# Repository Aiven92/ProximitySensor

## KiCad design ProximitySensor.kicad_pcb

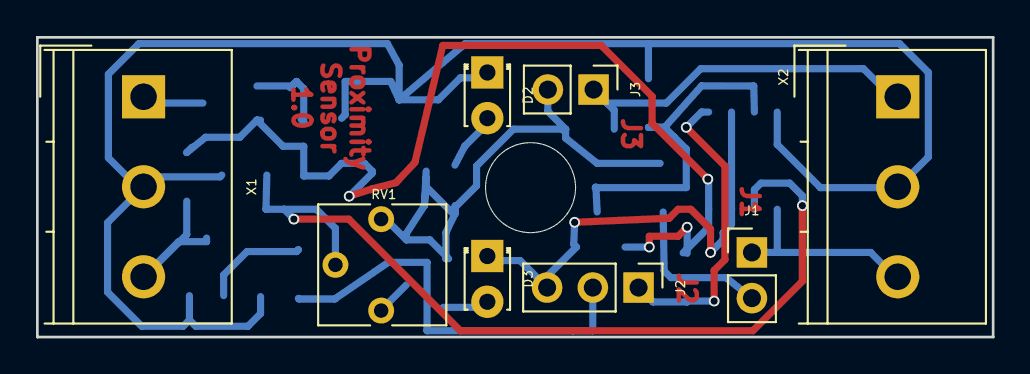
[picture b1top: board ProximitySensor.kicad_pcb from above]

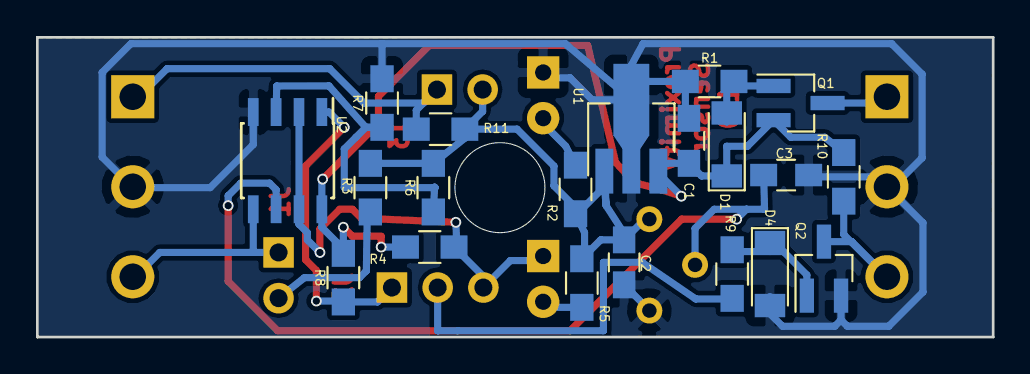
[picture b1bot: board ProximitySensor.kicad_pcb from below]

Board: 2 copper layers, 53.1 x 16.7 mm, 28 parts (20 on the bottom side), 17 nets.

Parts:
C1: 0,33uF; C_0805_HandSoldering
C2, C3: 0,1uF; C_0805_HandSoldering
D1, D4: D_Zener; D_MiniMELF
D2: LED_POWER; LED_D1.8mm_W3.3mm_H2.4mm
D3: LED_SIGNAL; LED_D1.8mm_W3.3mm_H2.4mm
J1, J3: Conn_01x02_Male; Pin_Header_Straight_1x02_Pitch2.54mm
J2: Conn_01x03_Male; Pin_Header_Straight_1x03_Pitch2.54mm
Q1: Q_PMOS_GSD; SOT-23_Handsoldering
Q2: Q_NMOS_GSD; SOT-23_Handsoldering
R1: 100k; R_0805_HandSoldering
R2, R5, R11: 1K; R_0805_HandSoldering
R3, R4, R6, R7, R8, R10: 10K; R_0805_HandSoldering
R9: 100R; R_0805_HandSoldering
RV1: 10k; Potentiometer_Trimmer_Vishay_T73YP_Horizontal
U1: L78L05_SOT89; SOT-89-3_Handsoldering
U2: LM393; SOIC-8_3.9x4.9mm_Pitch1.27mm
X1, X2: CONN_3; TerminalBlock_Philmore_TB133_03x5mm_Straight

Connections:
/5v: C2.1, J3.2, R2.1, R3.1, R5.1, R6.1, R11.2, RV1.1, U1.1
/Gnd: C1.2, C2.2, C3.2, D2.1, D4.2, Q2.2, R1.2, R7.2, RV1.3, U1.2, U2.4, X1.2, X2.2
/Vcc: C1.1, D1.1, Q1.2, R4.1, R8.2, R10.2, U1.3, U2.8
/in_v: Q1.3, X1.1
/sign: J1.1, U2.5, X2.3
unnamed: C3.1, RV1.2, U2.6
unnamed: D1.2, Q1.1, R1.1
unnamed: D2.2, R2.2
unnamed: D3.1, J2.3, R4.2, U2.2, U2.7
unnamed: D3.2, R5.2
unnamed: D4.1, Q2.1, R9.2
unnamed: J1.2, R3.2
unnamed: J2.1, R8.1, U2.1
unnamed: J2.2, R9.1
unnamed: J3.1, R11.1, X2.1
unnamed: Q2.3, R10.1, X1.3
unnamed: R6.2, R7.1, U2.3

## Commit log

2017-09-11 Init
2017-09-14 New topology
2017-09-18 add D_Zener
2017-09-27 add some small changes
